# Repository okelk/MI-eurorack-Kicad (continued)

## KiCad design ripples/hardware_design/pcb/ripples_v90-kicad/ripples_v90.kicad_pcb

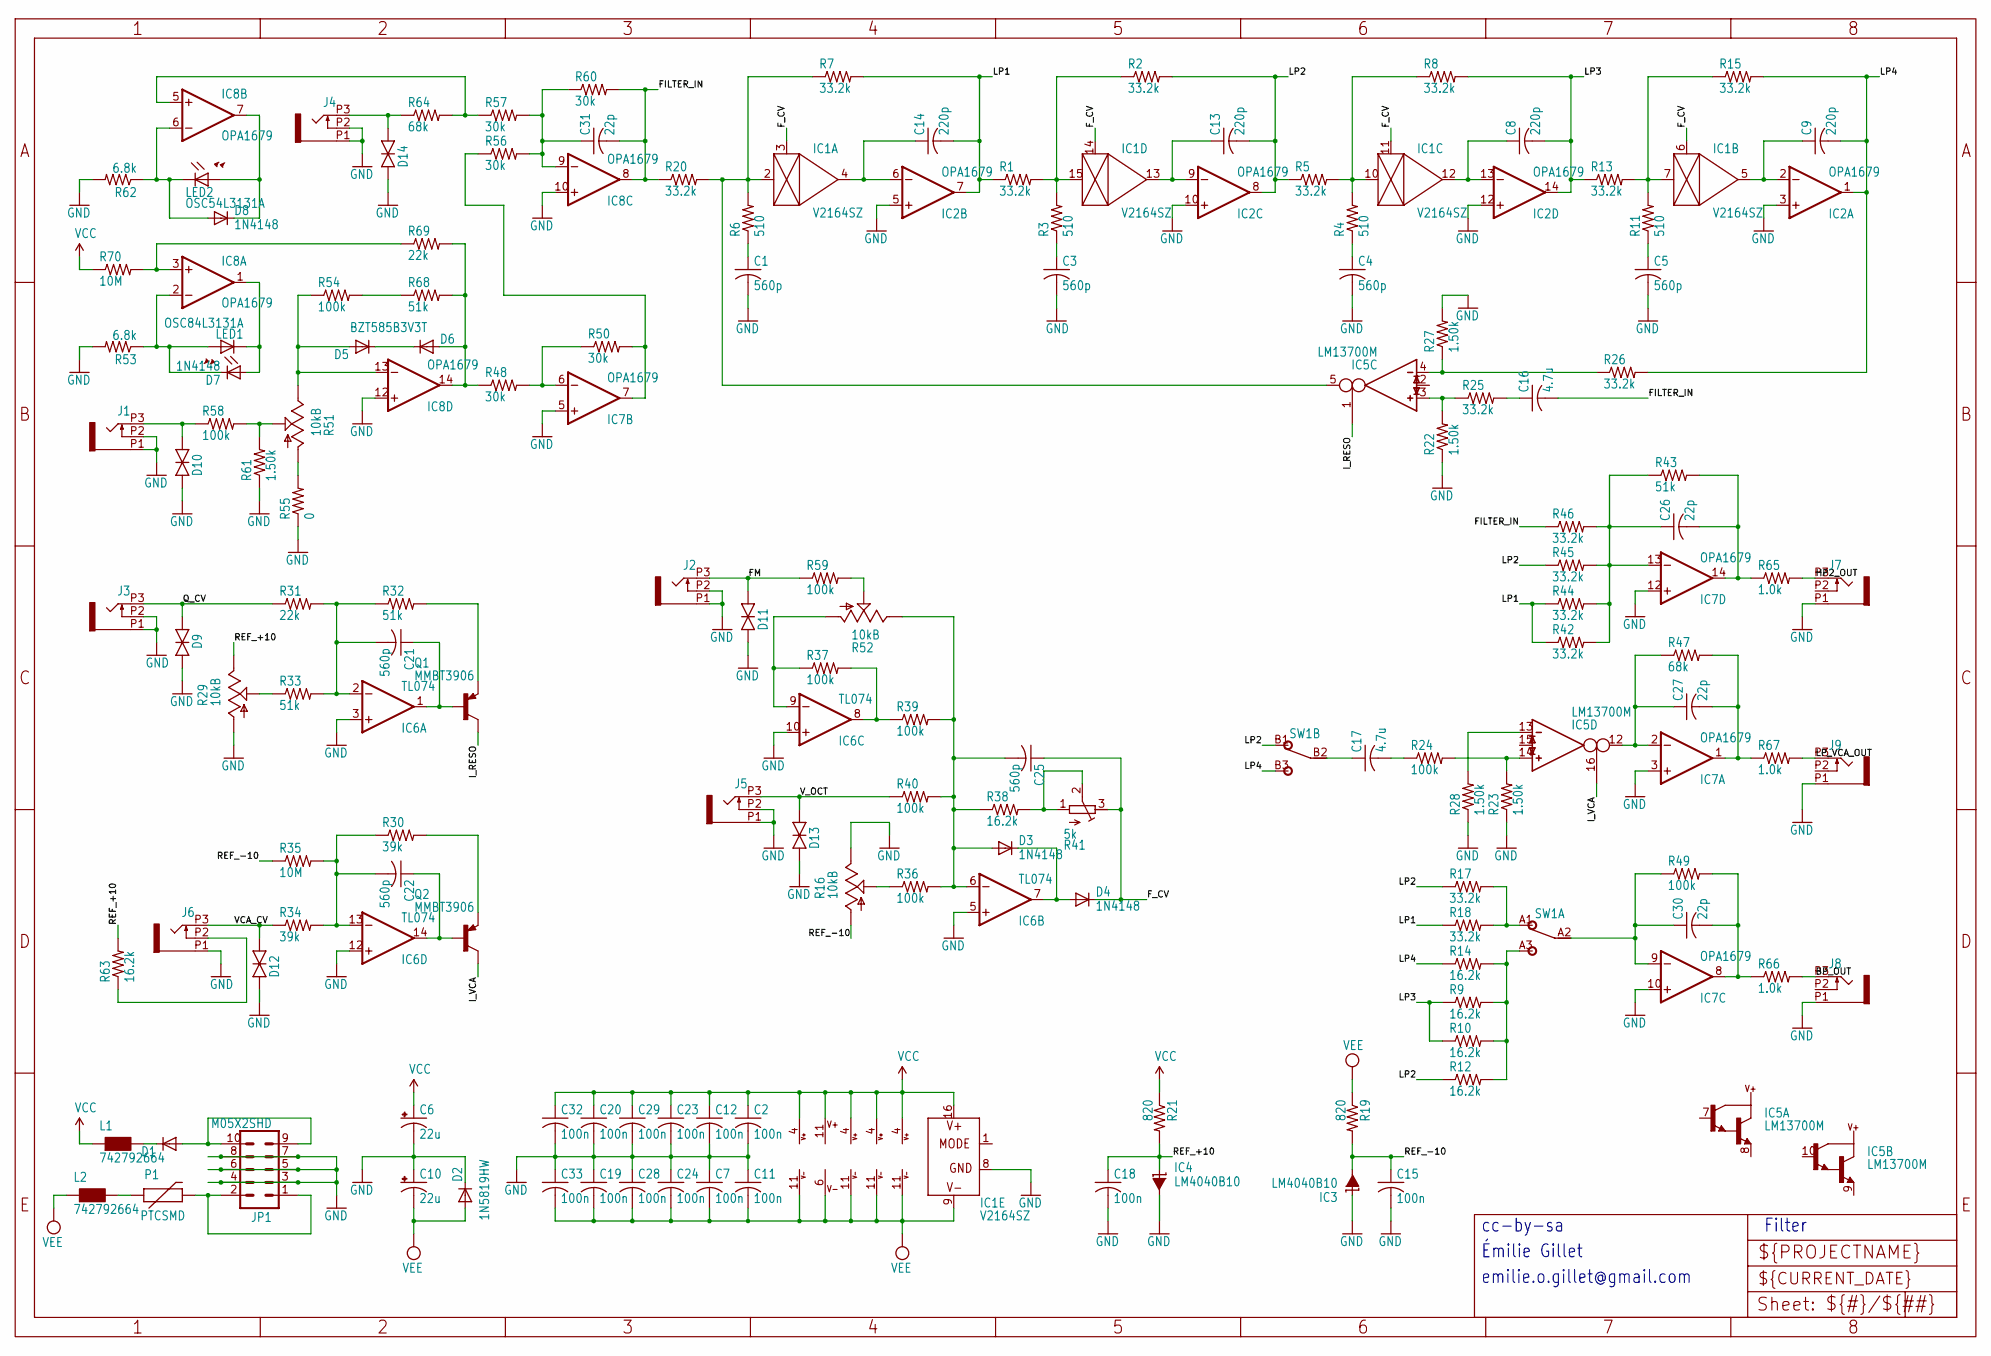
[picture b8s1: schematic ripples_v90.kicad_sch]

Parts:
C1, C3, C4, C5, C21, C22, C25: 560p; C0402
C2, C7, C11, C12, C15, C18, C19, C20, C23, C24, C28, C29, C32, C33: 100n; C0402
C6, C10: 22u; PANASONIC_B
C8, C9, C13, C14: 220p; C0603
C16, C17: 4.7u; C1206
C26, C27, C30, C31: 22p; C0402
D1, D2: 1N5819HW; SOD123
D3, D4, D7, D8: 1N4148; SOD523
D5, D6: BZT585B3V3T; SOD523
D9, D10, D11, D12, D13, D14: TVS; 0603
IC1: V2164SZ; SOIC16N
IC2, IC7, IC8: OPA1679; TSSOP14_065
IC3, IC4: LM4040B10; DBZ_R-PDSO-G3
IC5: LM13700M; SO16
IC6: TL074; TSSOP14_065
J1, J2, J3, J4, J5, J6, J7, J8, J9: PJ301_THONKICONNTME; WQP_PJ_301M_TME
JP1: M05X2SHD; 2X5-SHROUDED
L1, L2: 742792664; 0603
LED1: OSC84L3131A; LED3MM
LED2: OSC54L3131A; LED3MM
P1: PTCSMD; PTC-1206
Q1, Q2: MMBT3906; SOT23-BEC
R1, R2, R5, R7, R8, R13, R15, R17, R18, R20, R25, R26, R42, R44, R45, R46: 33.2k; R0402
R3, R4, R6, R11: 510; R0402
R9, R10, R12, R14, R38, R63: 16.2k; R0402
R16, R29: 10kB; ALPS_POT_VERTICAL_PS
R19, R21: 820; R0402
R22, R23, R27, R28, R61: 1.50k; R0402
R24, R36, R37, R39, R40, R49, R54, R58, R59: 100k; R0402
R30, R34: 39k; R0402
R31, R69: 22k; R0402
R32, R33, R43, R68: 51k; R0402
R35, R70: 10M; R0402
R41: 5k; RTRIM3296X
R47, R64: 68k; R0402
R48, R50, R56, R57, R60: 30k; R0402
R51, R52: 10kB; ALPS_POT_NARROW
R53, R62: 6.8k; R0402
R55: 0; R0402
R65, R66, R67: 1.0k; R0603
SW1: S-ON-ON-ONSS70070F-0202; SS70070F-0202

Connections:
BP_OUT: J8.P3 (3), R66.2
BP__OUT: C30.2, IC7.8 (OUT), R49.2, R66.1
CLEAN_IN: IC8.5 (+IN), R57.1, R64.2
CV_F_POT: R16.P$2 (S), R36.1
DIRTY_IN: D6.A, IC8.14 (OUT), R48.1, R68.2, R69.2
FILTER_IN: C16.2, C31.2, IC8.8 (OUT), R20.1, R46.1, R60.2
FM: D11.2 (C), J2.P3 (3), R59.1
F_CV: C25.1, D4.C, IC1.3 (CTRL), IC1.6 (CTRL), IC1.11 (CTRL), IC1.14 (CTRL), R41.3 (A)
GND: C1.2, C2.2, C3.2, C4.2, C5.2, C6.-, C7.1, C10.+, C11.1, C12.2, C15.2, C18.2, C19.1, C20.2, C23.2, C24.1, C28.1, C29.2, C32.2, C33.1, D2.C, D9.1 (A), D10.1 (A), D11.1 (A), D12.1 (A), D13.1 (A), D14.1 (A), IC1.8 (GND), IC2.3 (+IN), IC2.5 (+IN), IC2.10 (+IN), IC2.12 (+IN), IC3.1 (C), IC4.2 (A), IC6.3 (+IN), IC6.5 (+IN), IC6.10 (+IN), IC6.12 (+IN), IC7.3 (+IN), IC7.5 (+IN), IC7.10 (+IN), IC7.12 (+IN), IC8.10 (+IN), IC8.12 (+IN), J1.P1 (1), J1.P2 (2), J2.P1 (1), J2.P2 (2), J3.P1 (1), J3.P2 (2), J4.P1 (1), J4.P2 (2), J5.P1 (1), J5.P2 (2), J6.P1 (1), J7.P1 (1), J8.P1 (1), J9.P1 (1), JP1.3, JP1.4, JP1.5, JP1.6, JP1.7, JP1.8, R16.P$1 (E), R22.1, R23.1, R27.2, R28.1, R29.P$3 (A), R53.2, R55.1, R61.1, R62.2
HP2_OUT: J7.P3 (3), R65.2
HP2__OUT: C26.2, IC7.14 (OUT), R43.2, R65.1
I_RESO: IC5.1 (I_BIAS), Q1.C
I_VCA: IC5.16 (I_BIAS), Q2.C
LP1: C14.2, IC2.7 (OUT), R1.1, R7.2, R18.1, R42.1, R44.1
LP2: C13.2, IC2.8 (OUT), R2.2, R5.1, R12.1, R17.1, R45.1, SW1.B1 (1)
LP3: C8.2, IC2.14 (OUT), R8.2, R9.1, R10.1, R13.1
LP4: C9.2, IC2.1 (OUT), R14.1, R15.2, R26.2, SW1.B3 (3)
LP_VARIABLE: C17.1, SW1.B2 (2)
LP_VCA_OUT: J9.P3 (3), R67.2
LP_VCA__OUT: C27.2, IC7.1 (OUT), R47.2, R67.1
unnamed: IC6.8 (OUT), R37.2, R39.1
unnamed: C14.1, IC1.4 (OUT), IC2.6 (-IN)
unnamed: IC1.15 (IN), R1.2, R2.1, R3.2
unnamed: R38.2, R41.1 (E), R41.2 (S)
unnamed: IC7.6 (-IN), R48.2, R50.1
unnamed: D1.A, JP1.9, JP1.10
unnamed: C16.1, R25.2
unnamed: C1.1, R6.1
unnamed: C13.1, IC1.13 (OUT), IC2.9 (-IN)
unnamed: IC1.2 (IN), IC5.5 (OUT), R6.2, R7.1, R20.2
unnamed: C3.1, R3.1
unnamed: IC1.10 (IN), R4.2, R5.2, R8.1
unnamed: C8.1, IC1.12 (OUT), IC2.13 (-IN)
unnamed: IC5.4 (IN_N), R26.1, R27.1
unnamed: C4.1, R4.1
unnamed: IC1.7 (IN), R11.2, R13.2, R15.1
unnamed: C9.1, IC1.5 (OUT), IC2.2 (-IN)
unnamed: IC5.3 (IN_P), R22.2, R25.1
unnamed: C5.1, R11.1
unnamed: C26.1, IC7.13 (-IN), R42.2, R43.1, R44.2, R45.2, R46.2
unnamed: R52.P$2 (S), R59.2
unnamed: IC6.9 (-IN), R37.1, R52.P$3 (A)
unnamed: C25.2, D3.A, IC6.6 (-IN), R36.2, R38.1, R39.2, R40.2, R52.P$1 (E)
unnamed: R29.P$2 (S), R33.1
unnamed: C22.2, IC6.13 (-IN), R30.1, R34.2, R35.2
unnamed: C21.2, IC6.2 (-IN), R31.2, R32.1, R33.2
unnamed: C21.1, IC6.1 (OUT), Q1.B
unnamed: Q1.E, R32.2
unnamed: J6.P2 (2), R63.1
unnamed: C22.1, IC6.14 (OUT), Q2.B
unnamed: Q2.E, R30.2
unnamed: R51.P$3 (A), R55.2
unnamed: D7.A, IC8.1 (OUT), LED1.K (C)
unnamed: JP1.1, JP1.2, P1.2
unnamed: R54.2, R68.1
unnamed: D10.2 (C), J1.P3 (3), R58.1
unnamed: D7.C, IC8.2 (-IN), LED1.A, R53.1
unnamed: D3.C, D4.A, IC6.7 (OUT)
unnamed: IC7.7 (OUT), R50.2, R56.1
unnamed: C30.1, IC7.9 (-IN), R49.1, SW1.A2 (2)
unnamed: IC8.3 (+IN), R69.1, R70.2
unnamed: IC5.14 (IN_P), R23.2, R24.2
unnamed: C27.1, IC5.12 (OUT), IC7.2 (-IN), R47.1
unnamed: R51.P$2 (S), R58.2, R61.2
unnamed: D5.C, D6.C
unnamed: IC5.13 (IN_N), R28.2
unnamed: D1.C, L1.2
unnamed: L2.2, P1.1
unnamed: D14.2 (C), J4.P3 (3), R64.1
unnamed: C31.1, IC8.9 (-IN), R56.2, R57.2, R60.1
unnamed: D8.C, IC8.7 (OUT), LED2.A
unnamed: D8.A, IC8.6 (-IN), LED2.K (C), R62.1
unnamed: R17.2, R18.2, SW1.A1 (1)
unnamed: R9.2, R10.2, R12.2, R14.2, SW1.A3 (3)
unnamed: C17.2, R24.1
unnamed: D5.A, IC8.13 (-IN), R51.P$1 (E), R54.1
Q_CV: D9.2 (C), J3.P3 (3), R31.1
REF_+10: C18.1, IC4.1 (C), R21.2, R29.P$1 (E), R63.2
REF_-10: C15.1, IC3.2 (A), R16.P$3 (A), R19.2, R35.1
VCA_CV: D12.2 (C), J6.P3 (3), R34.1
VCC: C2.1, C6.+, C12.1, C20.1, C23.1, C29.1, C32.1, IC1.16 (V+), IC2.4 (V+), IC5.11 (V+), IC6.4 (V+), IC7.4 (V+), IC8.4 (V+), L1.1, R21.1, R70.1
VEE: C7.2, C10.-, C11.2, C19.2, C24.2, C28.2, C33.2, D2.A, IC1.9 (V-), IC2.11 (V-), IC5.6 (V-), IC6.11 (V-), IC7.11 (V-), IC8.11 (V-), L2.1, R19.1
V_OCT: D13.2 (C), J5.P3 (3), R40.1

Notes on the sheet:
emilie.o.gillet@gmail.com
Filter
cc-by-sa
Émilie Gillet

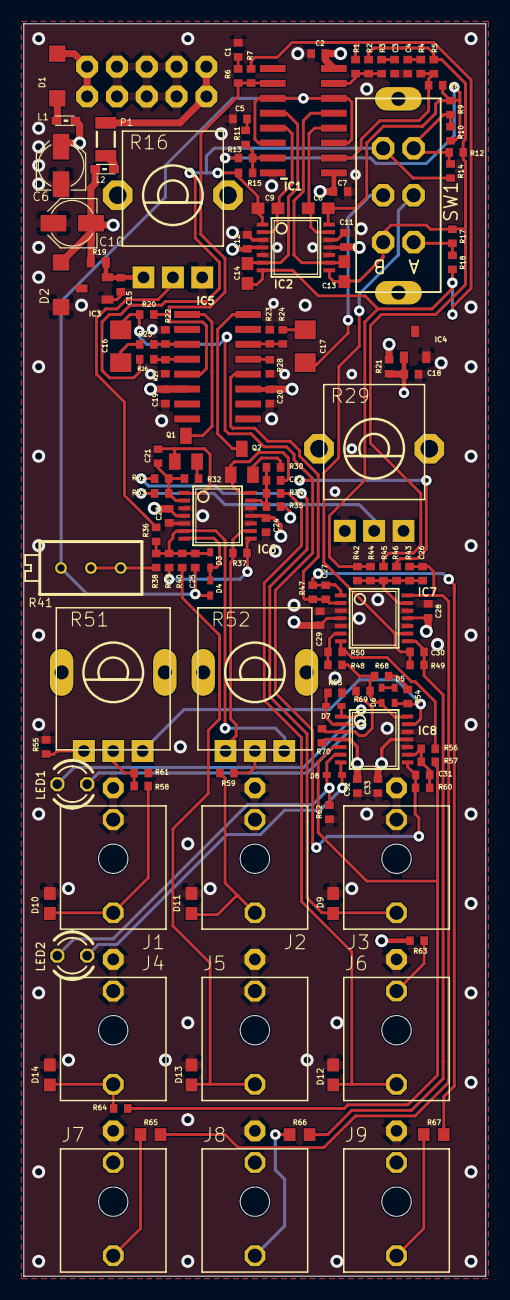
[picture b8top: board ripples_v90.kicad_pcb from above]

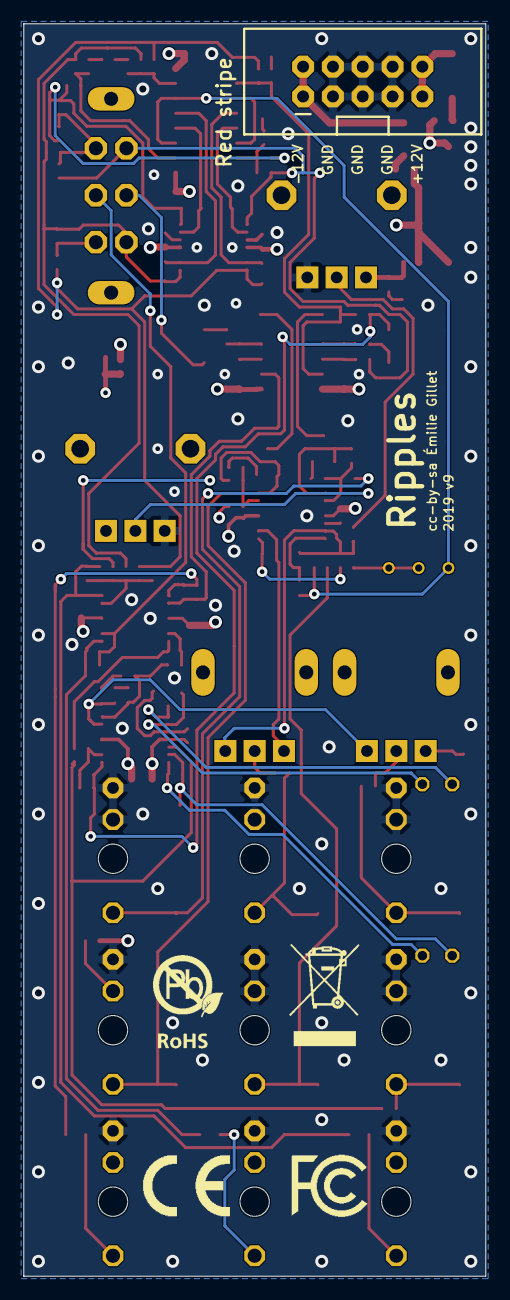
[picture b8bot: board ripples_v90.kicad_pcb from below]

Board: 4 copper layers, 39.3 x 106.7 mm, 147 parts (5 on the bottom side), 83 nets.

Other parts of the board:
U$1: CE_MEDIUM
U$2: FCC_MEDIUM
U$3: ROHS_LOGO
U$4: TRASHCAN_LOGO
